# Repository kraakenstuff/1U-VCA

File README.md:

# 1U-VCA
1U Eurorack VCA module adapted from Scott Bernardi's schematic (http://www.bernacomp.com/elec/og2/og2_dual_linear_vca.gif)

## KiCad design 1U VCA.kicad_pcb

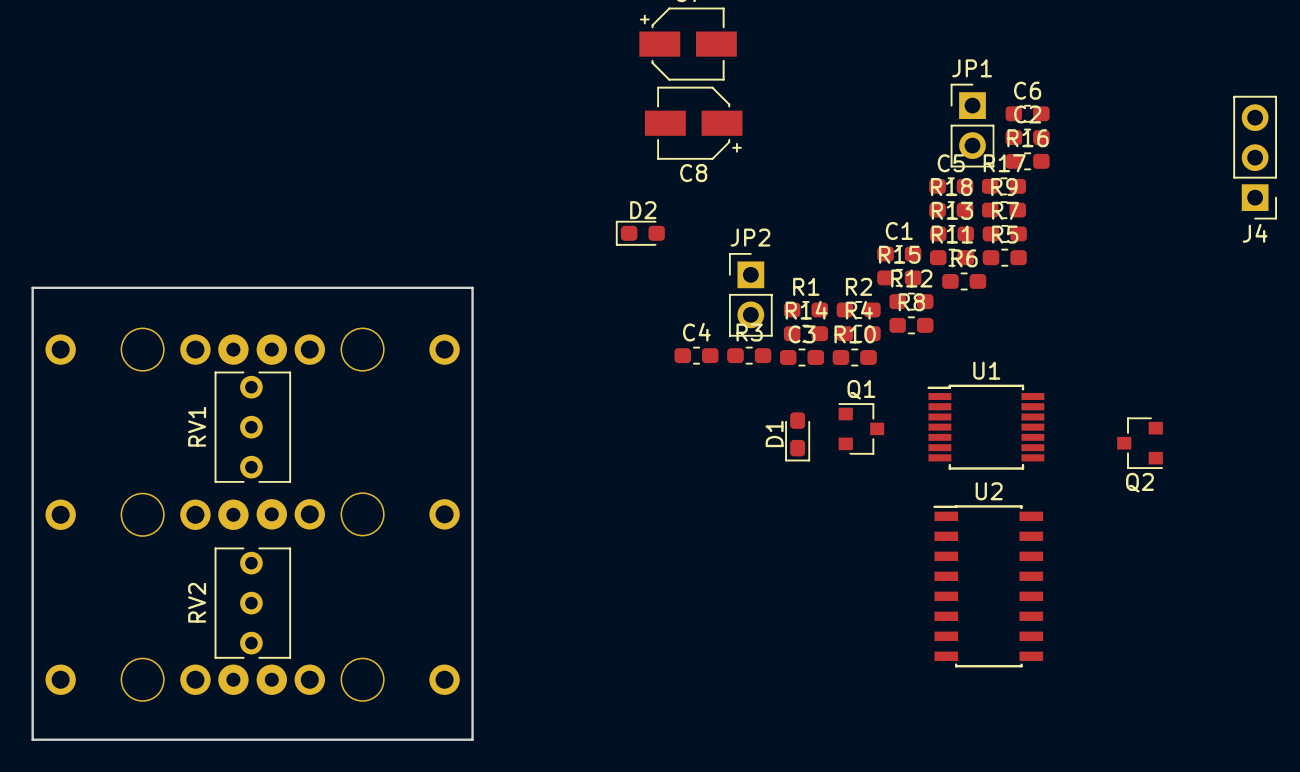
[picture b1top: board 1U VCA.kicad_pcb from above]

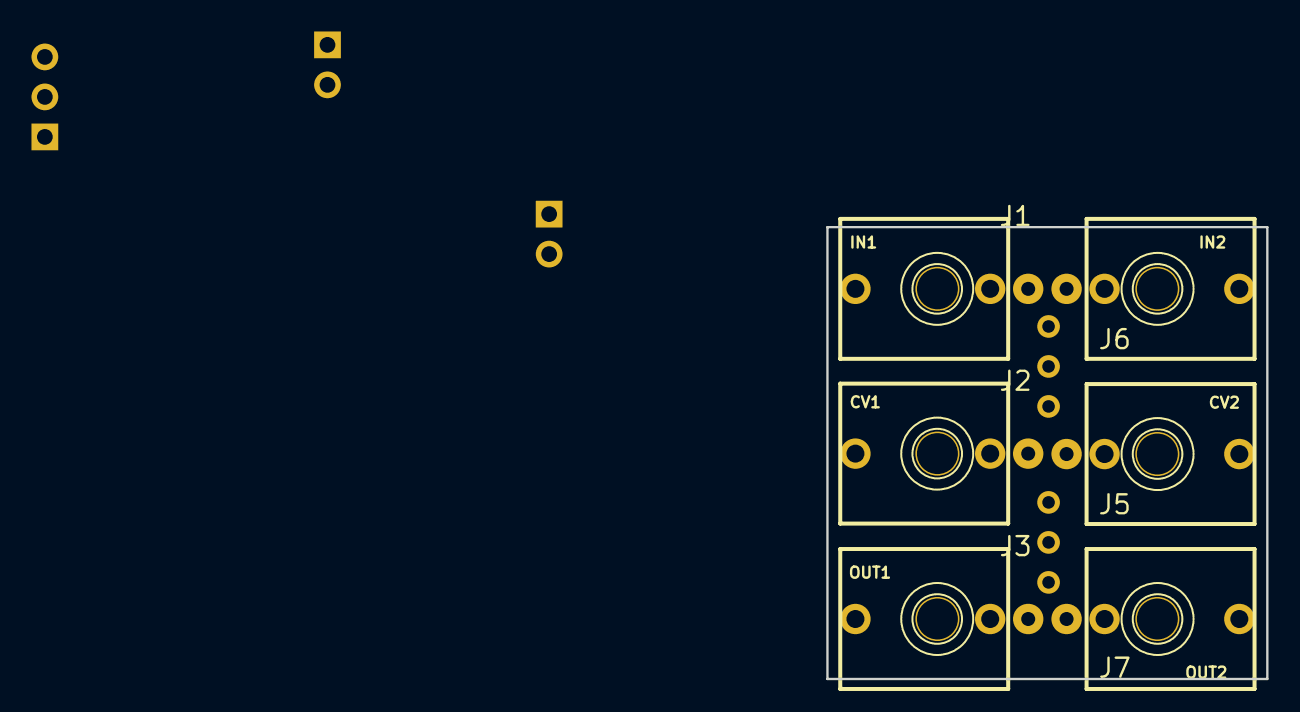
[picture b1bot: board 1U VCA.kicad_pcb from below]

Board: 2 copper layers, 27.9 x 28.7 mm, 43 parts (6 on the bottom side), 29 nets, no tracks yet.

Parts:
C1, C2, C3, C4, C5, C6: 100n; C_0603_1608Metric_Pad1.05x0.95mm_HandSolder
C7, C8: 10u; CP_Elec_4x5.4
D1, D2: 1N4148; D_0603_1608Metric_Pad1.05x0.95mm_HandSolder
J1: IN1; PJ301M-12
J2: CV1; PJ301M-12
J3: OUT1; PJ301M-12
J4: Conn_01x03; PinHeader_1x03_P2.54mm_Vertical
J5: CV2; PJ301M-12
J6: IN2; PJ301M-12
J7: OUT2; PJ301M-12
JP1, JP2: Jumper; PinHeader_1x02_P2.54mm_Vertical
Q1, Q2: MMBT3906; SOT-23
R1, R10: 1M; R_0603_1608Metric_Pad1.05x0.95mm_HandSolder
R2, R5, R11, R14: 390R; R_0603_1608Metric_Pad1.05x0.95mm_HandSolder
R3, R12: 15k; R_0603_1608Metric_Pad1.05x0.95mm_HandSolder
R4, R13: 100k; R_0603_1608Metric_Pad1.05x0.95mm_HandSolder
R6, R7, R15, R16: 20k; R_0603_1608Metric_Pad1.05x0.95mm_HandSolder
R8, R17: 39k; R_0603_1608Metric_Pad1.05x0.95mm_HandSolder
R9, R18: 300k; R_0603_1608Metric_Pad1.05x0.95mm_HandSolder
RV1, RV2: 100k; Potentiometer_Bourns_3266Y_Vertical
U1: TL074; TSSOP-14_4.4x5mm_P0.65mm
U2: LM13700; SOIC-16_3.9x9.9mm_P1.27mm

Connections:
+12V: C1.1, C3.1, C5.1, C7.1, J4.1, R3.2, R12.2, RV1.1, RV2.1, U1.4, U2.11
-12V: C2.2, C4.2, C6.2, C8.2, J4.3, RV1.3, RV2.3, U1.11, U2.6
GND: C1.2, C2.1, C3.2, C4.1, C5.2, C6.1, C7.2, C8.1, J1.S, J1.TN, J2.S, J2.TN, J3.S, J4.2, J5.S, J5.TN, J6.S, J6.TN, J7.S, R2.2, R5.2, R11.2, R14.2, U1.3, U1.5, U1.9, U1.13
unnamed: D1.1, Q1.2, R6.1, R7.1, U1.2
unnamed: D1.2, Q1.1, U1.1
unnamed: D2.1, Q2.2, R15.1, R16.1, U1.10
unnamed: D2.2, Q2.1, U1.8
unnamed: J1.T, R4.2
unnamed: J2.T, JP1.2, R7.2
unnamed: J3.T, R9.2, U1.7
unnamed: J5.T, JP2.2, R16.2
unnamed: J6.T, R13.2
unnamed: J7.T, R18.2, U1.14
unnamed: JP1.1, R6.2
unnamed: JP2.1, R15.2
unnamed: Q1.3, R8.1
unnamed: Q2.3, R17.1
unnamed: R1.1, R2.1, U2.4
unnamed: R1.2, RV1.2
unnamed: R3.1, U2.2
unnamed: R4.1, R5.1, U2.3
unnamed: R8.2, U2.1
unnamed: R9.1, U1.6, U2.5
unnamed: R10.1, R11.1, U2.13
unnamed: R10.2, RV2.2
unnamed: R12.1, U2.15
unnamed: R13.1, R14.1, U2.14
unnamed: R17.2, U2.16
unnamed: R18.1, U1.12, U2.12

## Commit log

2019-02-13 Not sure what was changed, but this is still not the final design
